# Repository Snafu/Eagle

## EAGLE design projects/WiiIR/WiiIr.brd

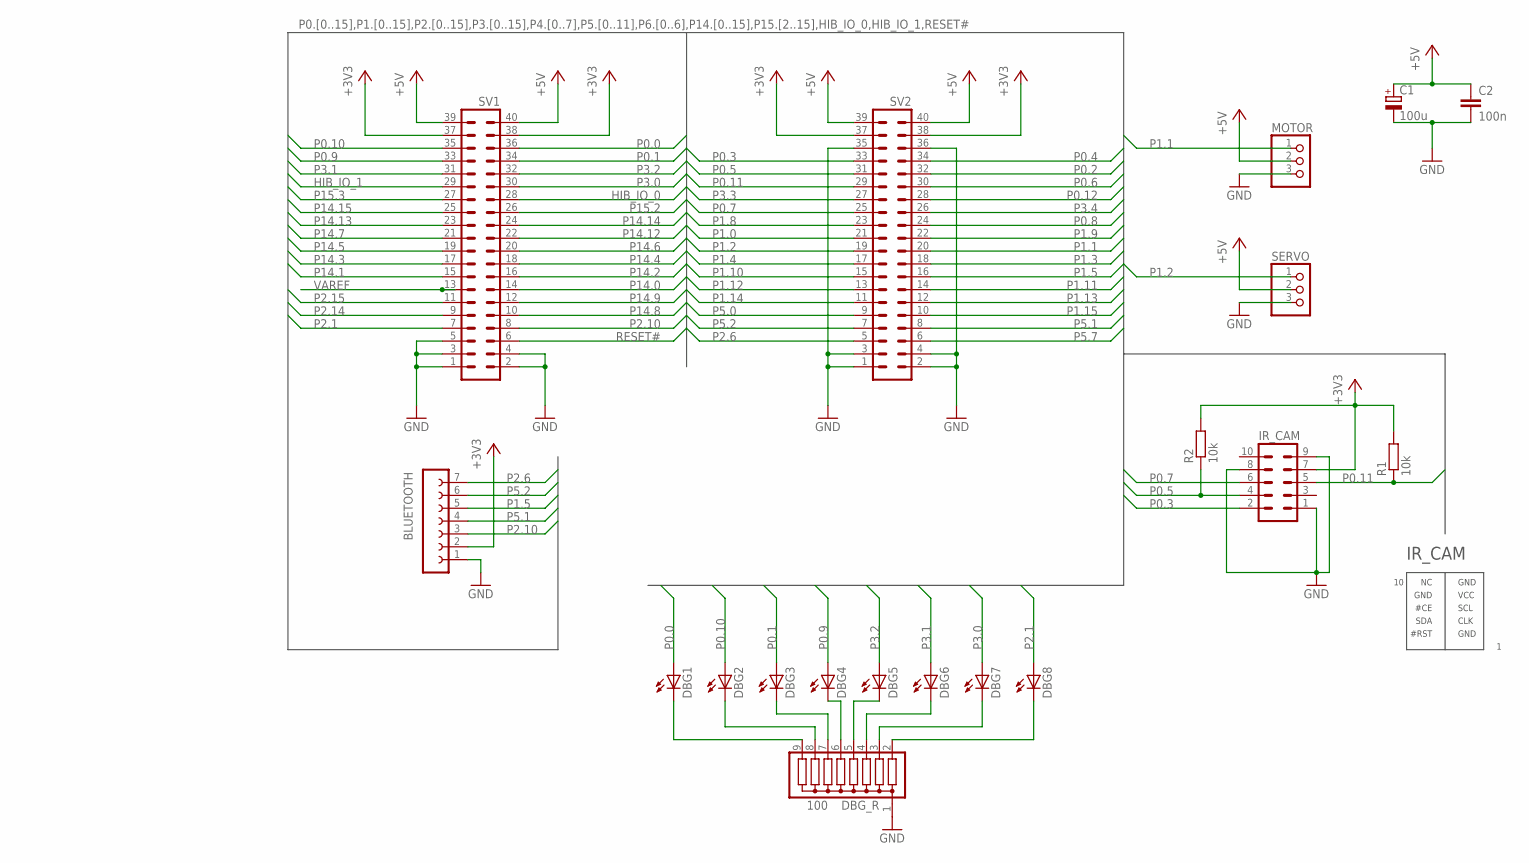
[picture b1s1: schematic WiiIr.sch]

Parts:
BLUETOOTH: FE07-1; FE07
C1: 100u; E2,5-7
C2: 100n; C025-025X050
DBG1, DBG2, DBG3, DBG4, DBG5, DBG6, DBG7, DBG8: LEDSQR2X5; LED2X5
DBG_R: 100; SIL9
IR_CAM: ML10
MOTOR: PINHD-1X3/90; 1X03/90
R1: 10k; 0207/12
R2: 10k; 0207/10
SERVO: PINHD-1X3/90; 1X03/90
SV1, SV2: MA20-2

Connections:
+3V3: BLUETOOTH.2, IR_CAM.7, R1.2, R2.2, SV1.37, SV1.38, SV2.37, SV2.38
+5V: C1.+, C2.1, MOTOR.2, SERVO.2, SV1.39, SV1.40, SV2.39, SV2.40
GND: BLUETOOTH.1, C1.-, C2.2, DBG_R.1, IR_CAM.1, IR_CAM.8, IR_CAM.9, MOTOR.3, SERVO.3, SV1.1, SV1.2, SV1.3, SV1.4, SV1.5, SV2.1, SV2.2, SV2.3, SV2.4, SV2.35, SV2.36
HIB_IO_0: SV1.28
HIB_IO_1: SV1.29
unnamed: DBG1.K (C), DBG_R.9
unnamed: DBG2.K (C), DBG_R.8
unnamed: DBG3.K (C), DBG_R.7
unnamed: DBG4.K (C), DBG_R.6
unnamed: DBG5.K (C), DBG_R.5
unnamed: DBG6.K (C), DBG_R.4
unnamed: DBG7.K (C), DBG_R.3
unnamed: DBG8.K (C), DBG_R.2
P0.0: DBG1.A, SV1.36
P0.1: DBG3.A, SV1.34
P0.2: SV2.32
P0.3: IR_CAM.2, SV2.33
P0.4: SV2.34
P0.5: IR_CAM.4, R2.1, SV2.31
P0.6: SV2.30
P0.7: IR_CAM.6, SV2.25
P0.8: SV2.24
P0.9: DBG4.A, SV1.33
P0.10: DBG2.A, SV1.35
P0.11: IR_CAM.5, R1.1, SV2.29
P0.12: SV2.28
P1.0: SV2.21
P1.1: MOTOR.1, SV2.20
P1.2: SERVO.1, SV2.19
P1.3: SV2.18
P1.4: SV2.17
P1.5: BLUETOOTH.5, SV2.16
P1.8: SV2.23
P1.9: SV2.22
P1.10: SV2.15
P1.11: SV2.14
P1.12: SV2.13
P1.13: SV2.12
P1.14: SV2.11
P1.15: SV2.10
P2.1: DBG8.A, SV1.7
P2.6: BLUETOOTH.7, SV2.5
P2.10: BLUETOOTH.3, SV1.8
P2.14: SV1.9
P2.15: SV1.11
P3.0: DBG7.A, SV1.30
P3.1: DBG6.A, SV1.31
P3.2: DBG5.A, SV1.32
P3.3: SV2.27
P3.4: SV2.26
P5.0: SV2.9
P5.1: BLUETOOTH.4, SV2.8
P5.2: BLUETOOTH.6, SV2.7
P5.7: SV2.6
P14.0: SV1.14
P14.1: SV1.15
P14.2: SV1.16
P14.3: SV1.17
P14.4: SV1.18
P14.5: SV1.19
P14.6: SV1.20
P14.7: SV1.21
P14.8: SV1.10
P14.9: SV1.12
P14.12: SV1.22
P14.13: SV1.23
P14.14: SV1.24
P14.15: SV1.25
P15.2: SV1.26
P15.3: SV1.27
RESET#: SV1.6
VAREF: SV1.13

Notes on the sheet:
GND
VCC
SCL
#CE
CLK
SDA
#RST
IR_CAM

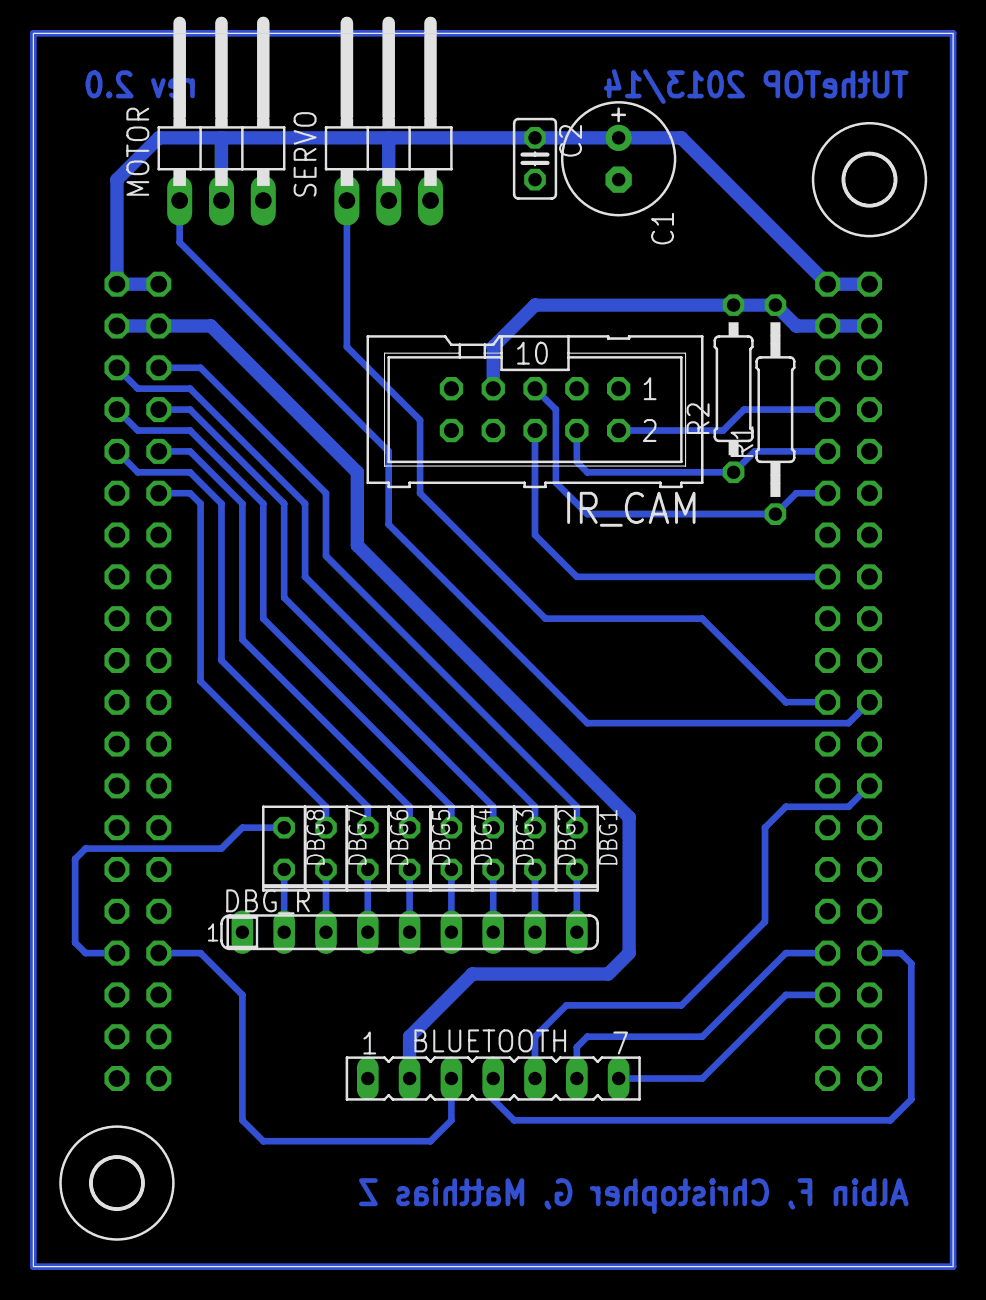
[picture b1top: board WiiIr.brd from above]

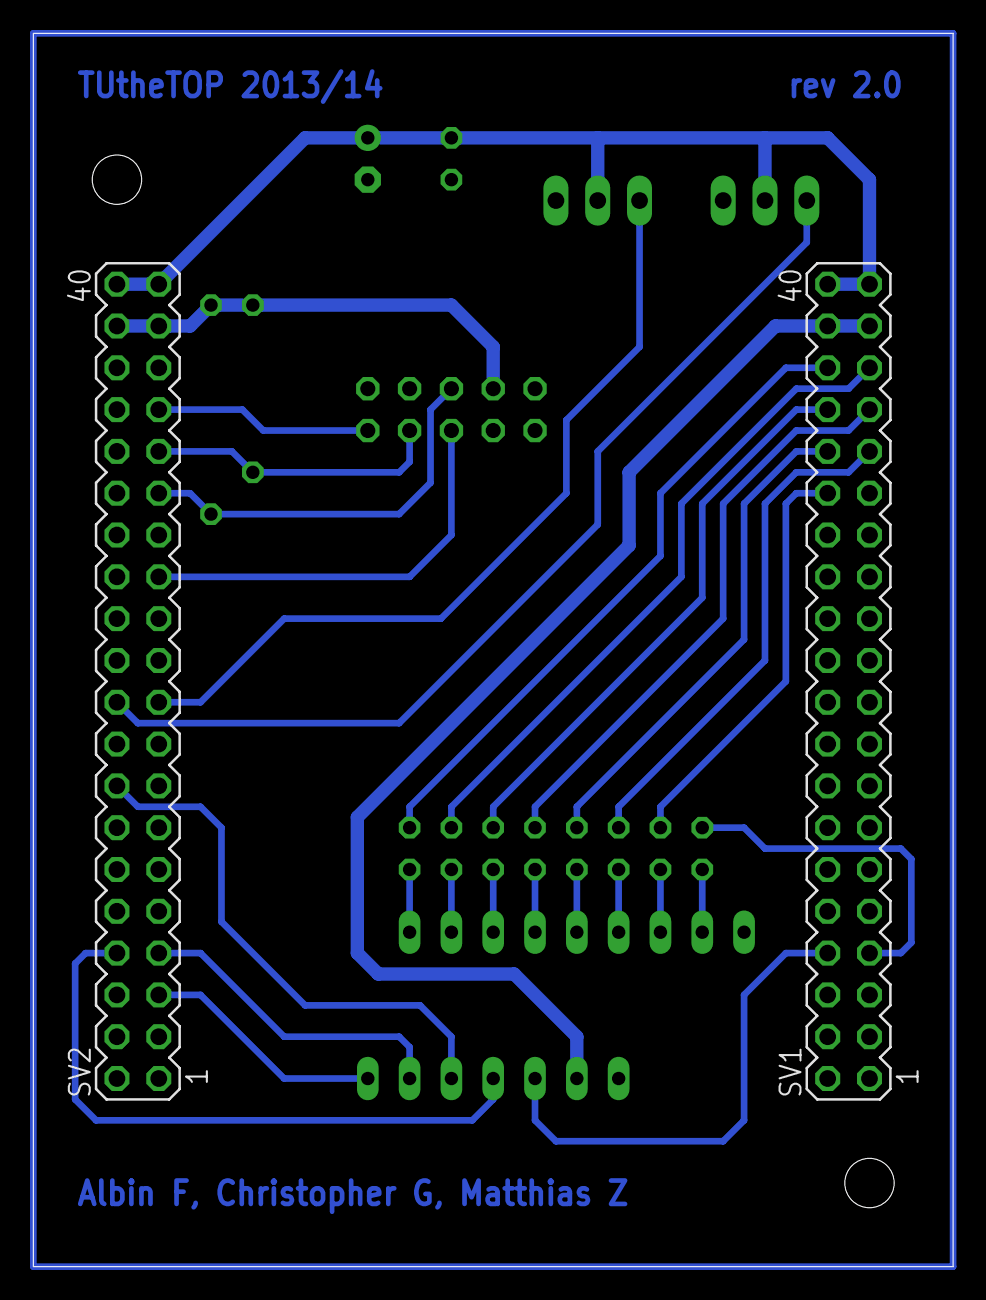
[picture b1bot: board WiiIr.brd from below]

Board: 2 copper layers, 55.9 x 74.9 mm, 21 parts (2 on the bottom side), 30 nets.

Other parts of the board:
U$1, U$2: 3,0

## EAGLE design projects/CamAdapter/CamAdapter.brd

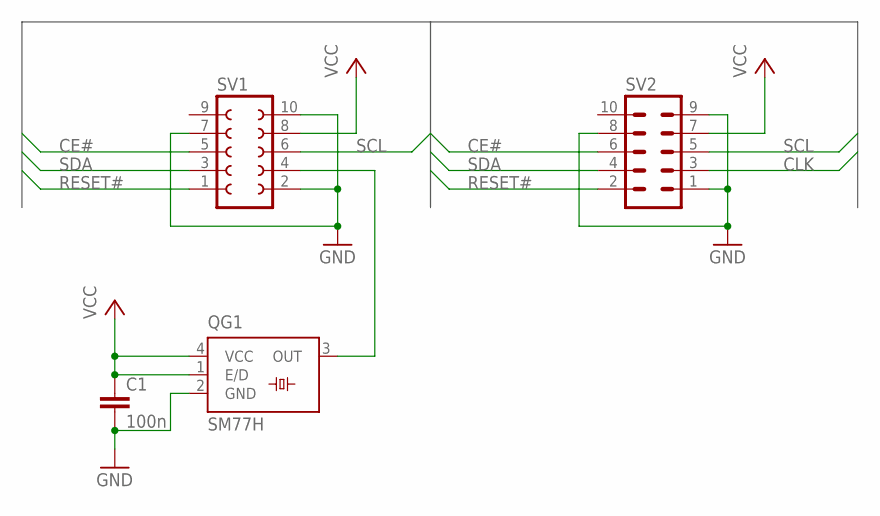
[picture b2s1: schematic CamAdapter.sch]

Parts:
C1: 100n; C0805
QG1: SM77H
SV1: FE05-2
SV2: ML10

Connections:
CE#: SV1.5, SV2.6
CLK: SV2.3
GND: C1.2, QG1.2 (GND), SV1.2, SV1.7, SV1.10, SV2.1, SV2.8, SV2.9
unnamed: QG1.3 (OUT), SV1.4
RESET#: SV1.1, SV2.2
SCL: SV1.6, SV2.5
SDA: SV1.3, SV2.4
VCC: C1.1, QG1.1 (E/D), QG1.4 (VCC), SV1.8, SV2.7

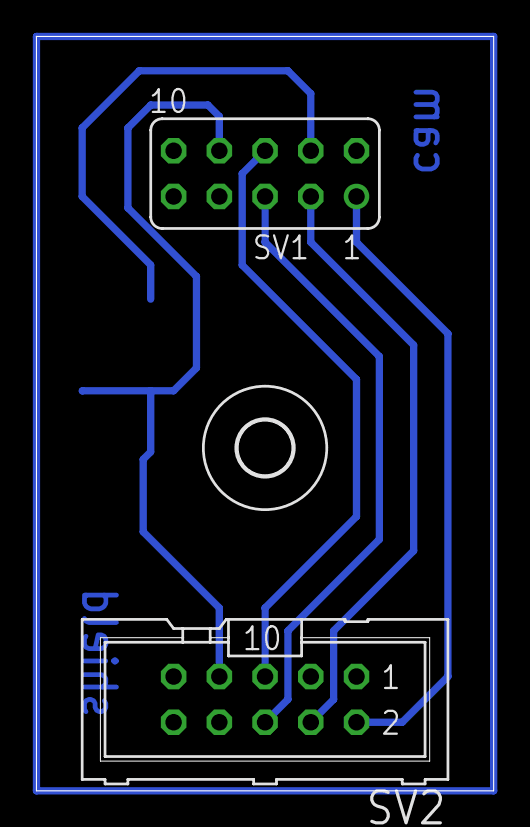
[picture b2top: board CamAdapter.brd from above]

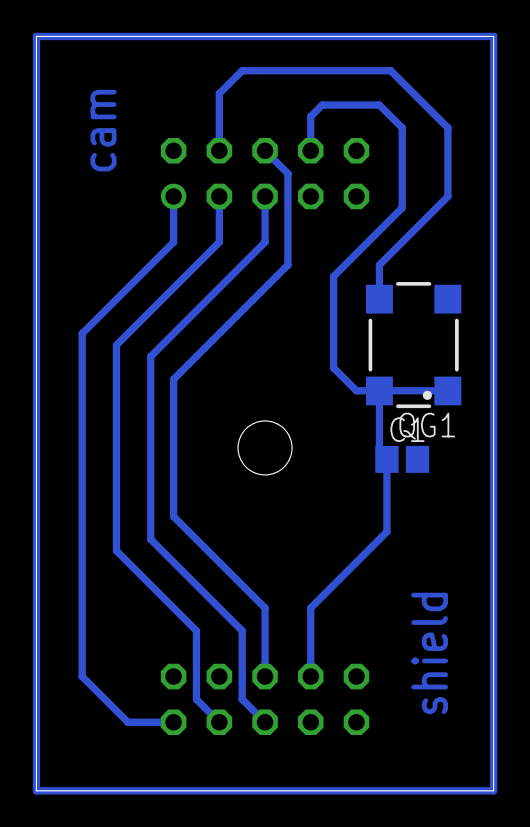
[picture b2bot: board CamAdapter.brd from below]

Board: 2 copper layers, 25.4 x 41.9 mm, 5 parts (2 on the bottom side), 7 nets.

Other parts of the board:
U$1: 3,0

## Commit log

2014-03-24 CamAdapter + XMC Shield
2014-03-24 XMC Shield servo caps
2014-03-25 Bent pin headers for servo
2014-03-26 Board updates + gcode
2014-03-28 Restructured + PCB v1 issues solved
2014-03-28 IR_CAM description, optimizations
2014-04-01 Updated CamAdapter + Board
    * Added 25 MHz resonator to adapter board
    * Removed 25 MHz CLK signal from PCB connector
2014-04-01 Rev 2.0 RC
    * TODO: Check CamAdapter.brd quarz oscillator package
2014-04-01 Fixed forgotten SCL line
2014-04-02 Enhaced space between signal trace and female pin header
2014-04-02 pcb2gcode.cam update + new .gbr and .drd files
2014-04-02 pcb2gcode executed
2014-04-02 Removed deprecated files
2014-04-04 Changed millproject file
    * Milldrill with 0.0236mil (0.6mm) mill head
2014-04-04 pcb2gcode.cam updated
    * Do _not_ mirror back and outline layer
2014-04-04 New pcb2gcode output from last commit
2014-04-04 pcb2gcode outline & drill test
2014-04-06 Final
    * finally found out pcb2gcode and CAM settings so that
    lower right corner is origin and coordinates relative to that point
    lign up when CNC milling
